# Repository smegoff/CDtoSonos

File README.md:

# CDtoSonos

CDtoSonos turns an NAD C541i CD player into a lossless, hands-free Sonos
source. A Heltec WiFi LoRa 32 V3 captures the player's native
16-bit/44.1 kHz stereo PCM bus, wraps it in FLAC, and serves it directly to the
coordinator of an existing Sonos room or group.

Once provisioned, the appliance needs no web interaction:

1. Connect to Wi-Fi.
2. Discover and remember the selected Sonos coordinator.
3. Wait for sustained CD audio.
4. Start the lossless stream automatically.
5. Ignore normal track gaps and stop after prolonged silence.
6. Reconnect automatically if the Sonos client drops.

The firmware never changes Sonos groups, bonding, surrounds, Sub, Trueplay, EQ,
mute, or volume.

## Current hardware

- NAD C541i CD player
- Heltec WiFi LoRa 32 V3 (ESP32-S3)
- SN74LVC245AN or compatible 74LVC245 in DIP-20
- Three 1 kΩ resistors
- One 100 nF ceramic decoupling capacitor
- Stripboard/veroboard, headers, insulated hookup wire and heat-shrink
- USB power for the Heltec during the validated build

See [the complete hardware, vero-board and KiCad PCB guide](docs/hardware/README.md)
before working inside the player.

The carrier can also live outside the CD player in the
[3D-printed OLED/USB-C enclosure](hardware/enclosure/heltec-external-case/README.md),
connected by a deliberately short screened four-core lead.

## Features

- Native CD sample rate and word length; no resampling
- Stereo FLAC stream at `http://cdtosonos.local:8000/cd.flac`
- Automatic Sonos discovery, saved coordinator and audio-triggered playback
- 1.5-second audio qualification and 90-second track-gap/silence holdoff
- Sonos-specific stream recovery for stalls and large skips during playback
- Ten-band graphic EQ with presets, custom settings and a true Flat bypass
- Responsive web dashboard with spectrum analyser, analogue VU meters,
  access-point diagnostics, Wi-Fi setup and manual Sonos controls
- OLED status display
- SX1262 LoRa radio held in hardware reset and never used by the firmware
- mDNS hostname `http://cdtosonos.local/`

## Firmware build

For an optional PC-side CRC/decode check of a live stream, see the
[on-demand stream integrity test](docs/stream-integrity.md). It requires no
firmware update and saves diagnostics, not audio.

Install [PlatformIO](https://platformio.org/), then:

```sh
cd firmware/heltec-v3
pio run
pio run --target upload --upload-port COM13
pio device monitor --port COM13 --baud 115200
```

The project is pinned to PlatformIO Espressif32 6.13.0 and ESP-IDF 5.5.3.
ESP-IDF build paths should not contain spaces. On Windows, clone the repository
to a short path such as `C:\CDtoSonos`.

Wi-Fi credentials and the preferred Sonos coordinator are stored only in the
ESP32's NVS flash. They are not compiled into this repository.

## Validated prototype

The hardware prototype has been validated with:

- 44.1 kHz source clock detection
- correct 16-bit right-justified PCM extraction from 24-bit slots
- independently decoded live FLAC frames
- automatic discovery and playback through a bonded Arc/Sub/Fives room
- automatic coordinator restoration after reboot
- sustained streaming with zero audio-ring overruns
- approximately 3% normal CPU use with the dashboard available

The current image uses approximately 45.4% of RAM and 28.3% of the 3 MB
application partition.

## Raspberry Pi prototype

The earlier Raspberry Pi/USB-audio implementation remains under `src/`,
`deploy/`, and `scripts/` for reference. The Heltec firmware is the current
standalone implementation and does not require a Raspberry Pi or Icecast.

## Metadata

The PCM bus contains audio samples but no CDDB, MusicBrainz or CD-Text data.
The FLAC transport can be extended with metadata, but automatic album and track
identification will require an additional disc-TOC connection or an online
audio-fingerprint service.

## Safety

The NAD contains hazardous mains voltage even though the digital signals used
by this project are low voltage. Unplug it before opening the case and keep all
new wiring and boards away from the mains inlet, switch, transformer primary
and exposed power-supply conductors.

Do not connect NAD `D+5V` to the Heltec. The validated prototype powers the
Heltec by USB and shares only digital ground with the NAD. An internal power
supply is intentionally outside the validated design.

This is a personal hardware modification, not a manufacturer-approved product.

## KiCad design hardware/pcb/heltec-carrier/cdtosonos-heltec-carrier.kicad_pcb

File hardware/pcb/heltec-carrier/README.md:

# Heltec V3 carrier PCB

This directory contains the editable KiCad 10 source and manufacturing outputs
for revision A of the CDtoSonos Heltec carrier.

## Design

- Board: 92 x 60 mm, two copper layers, 1.6 mm FR-4.
- Controller: Heltec WiFi LoRa 32 V3 in two removable 1 x 18 sockets.
- Buffer: socketed SN74LVC245AN, fixed A-to-B direction.
- Input: J1 is currently a 2.54 mm 1 x 4 through-hole header.
- Protection: R1-R3 are 1 k series resistors.
- Decoupling: C1 is 100 nF directly beside U1.
- Ground: filled bottom-layer ground plane.
- Mounting: four M3 holes.

The 3D preview shows the sockets, not a Heltec module, because this project does
not bundle a custom Heltec 3D model.

## Files

- `cdtosonos-heltec-carrier.kicad_sch` - editable schematic.
- `cdtosonos-heltec-carrier.kicad_pcb` - editable routed PCB.
- `erc-report.txt` - KiCad electrical rules report.
- `drc-report.txt` - KiCad design, connectivity and schematic-parity report.
- `fabrication/` - Gerbers, Excellon drill files, drill maps and drill report.
- `cdtosonos-heltec-carrier-gerbers.zip` - upload package for a board house.
- `previews/` - top and bottom 3D renders.
- `../../../output/pdf/cdtosonos-heltec-carrier-schematic.pdf` - schematic PDF.
- `../../../output/pdf/cdtosonos-heltec-carrier-1to1.pdf` - actual-size fit sheet.
- `generate_kicad.py` - deterministic board and schematic generator.
- `build.ps1` - regeneration, checking and export script.
- `../../enclosure/heltec-external-case/` - printable external enclosure,
  connector plate, wiring drawing and fit-check assembly.

## Verified CAD status

KiCad 10.0.5 reports:

- 0 ERC violations;
- 0 DRC violations;
- 0 unconnected pads; and
- 0 schematic-parity issues.

That validates the CAD data, not the mechanical fit. Revision A has not yet
been physically fabricated or fitted inside the NAD.

## Mandatory fit check

Before ordering:

1. Print the 1:1 PDF using **Actual size** or **100%**. Do not use Fit,
   Shrink or Scale to page.
2. Confirm the printed outside dimensions are exactly 92 x 60 mm.
3. Place the actual Heltec and both purchased socket strips over the print.
4. Confirm the 22.86 mm socket-row spacing and pin-1 orientation.
5. Check J1 against the connector you intend to use. Change its footprint if
   it is not a plain 2.54 mm header.
6. Test the paper outline inside the unplugged NAD with the lid and transport
   clearances considered.

Treat the first manufactured board as a prototype.

## Regenerate

Install KiCad 10 and the small Python file-format helper:

```powershell
winget install --id KiCad.KiCad --exact
& "$env:LOCALAPPDATA\Programs\KiCad\10.0\bin\python.exe" -m pip install kiutils==1.4.8
```

Then run:

```powershell
.\hardware\pcb\heltec-carrier\build.ps1 -Render
```

The build fails if ERC, DRC, routing connectivity or schematic parity fail.

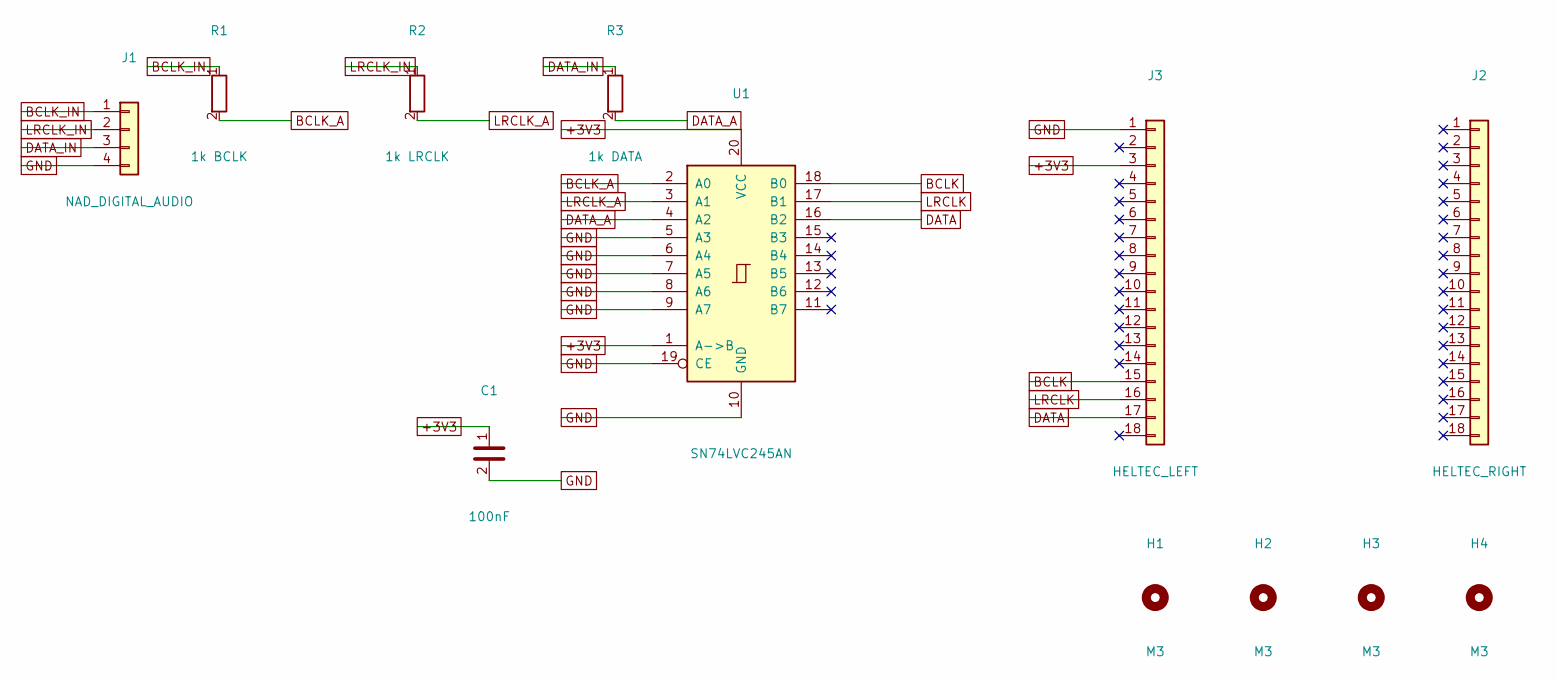
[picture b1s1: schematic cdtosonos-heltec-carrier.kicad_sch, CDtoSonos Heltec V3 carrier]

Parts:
C1: 100nF; C_Disc_D5.0mm_W2.5mm_P2.50mm
H1, H2, H3, H4: M3; MountingHole_3.2mm_M3
J1: NAD_DIGITAL_AUDIO; PinHeader_1x04_P2.54mm_Vertical
J2: HELTEC_RIGHT; PinSocket_1x18_P2.54mm_Vertical
J3: HELTEC_LEFT; PinSocket_1x18_P2.54mm_Vertical
R1: 1k BCLK; R_Axial_DIN0204_L3.6mm_D1.6mm_P5.08mm_Horizontal
R2: 1k LRCLK; R_Axial_DIN0204_L3.6mm_D1.6mm_P5.08mm_Horizontal
R3: 1k DATA; R_Axial_DIN0204_L3.6mm_D1.6mm_P5.08mm_Horizontal
U1: SN74LVC245AN; DIP-20_W7.62mm

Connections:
+3V3: C1.1, J3.3, U1.1 (A->B), U1.20 (VCC)
BCLK: J3.15, U1.18 (B0)
BCLK_A: R1.2, U1.2 (A0)
BCLK_IN: J1.1, R1.1
DATA: J3.17, U1.16 (B2)
DATA_A: R3.2, U1.4 (A2)
DATA_IN: J1.3, R3.1
GND: C1.2, J1.4, J3.1, U1.5 (A3), U1.6 (A4), U1.7 (A5), U1.8 (A6), U1.9 (A7), U1.10 (GND), U1.19 (CE)
LRCLK: J3.16, U1.17 (B1)
LRCLK_A: R2.2, U1.3 (A1)
LRCLK_IN: J1.2, R2.1

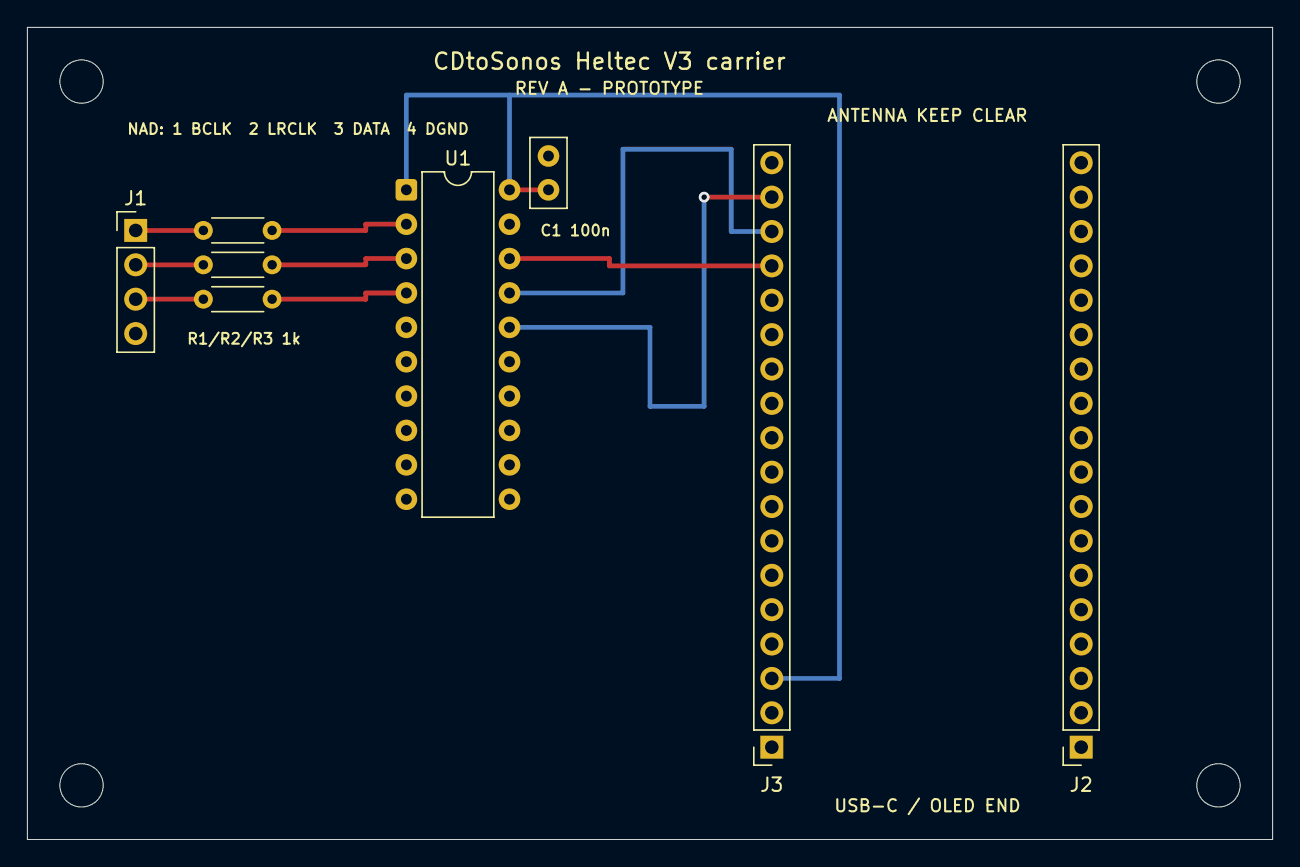
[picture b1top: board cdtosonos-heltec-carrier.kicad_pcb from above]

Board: 2 copper layers, 92.0 x 60.0 mm, 12 parts (0 on the bottom side), 11 nets.

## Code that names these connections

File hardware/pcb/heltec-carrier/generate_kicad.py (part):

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    for pin in range(11, 16):
        annotations.append(f"NoConn ~ 4800 {3000 + pin * 100}\n")

    # J3 pins: 1 GND, 3 3V3, 15 GPIO4/BCLK, 16 GPIO5/LRCLK, 17 GPIO6/DATA.
    for pin, net in ((1, "GND"), (3, "+3V3"), (15, "BCLK"), (16, "LRCLK"), (17, "DATA")):
        annotations.append(label(net, 7300, 3050 + pin * 100))
    for pin in [2, *range(4, 15), 18]:
        annotations.append(f"NoConn ~ 7300 {3050 + pin * 100}\n")
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Text Notes 1200 1200 0    100  ~ 20
CDtoSonos Heltec V3 carrier
Text Notes 1200 1450 0    60   ~ 12
J1: 1 BCLK, 2 LRCLK, 3 DATA, 4 DGND. U1 is represented by physical DIP pin number.
""" + "".join(parts) + "".join(annotations) + "$EndSCHEMATC\n"
    LEGACY_SCH_PATH.write_text(schematic, encoding="ascii")

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        )

    # J1 and the three series resistors.
    for pin, net in enumerate(("BCLK_IN", "LRCLK_IN", "DATA_IN", "GND"), 1):
        x, y = find_pin_position(library_symbols["J1"], pin, 35.56, 60.96)
        connect_global_label(schematic, net, x, y, 20.32)
    for resistor_x, source, buffered in (
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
